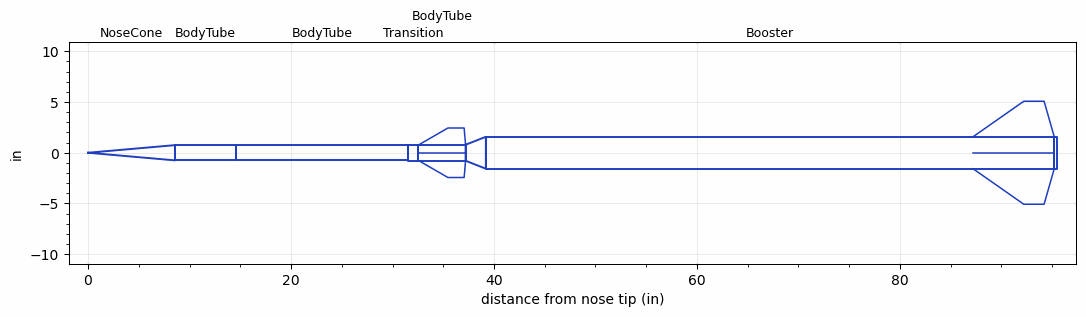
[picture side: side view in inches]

<RASAeroDocument>
 <FileVersion>2</FileVersion>
 <RocketDesign>
  <NoseCone>
   <Length>8.57</Length>
   <Diameter>1.5</Diameter>
   <Shape>Conical</Shape>
   <BluntRadius>0.065</BluntRadius>
   <Location>0</Location>
  </NoseCone>
  <BodyTube>
   <Length>6</Length>
   <Diameter>1.5</Diameter>
   <Location>8.57</Location>
  </BodyTube>
  <BodyTube>
   <Length>16.98</Length>
   <Diameter>1.5</Diameter>
   <Location>14.57</Location>
  </BodyTube>
  <Transition>
   <Length>1</Length>
   <Diameter>1.575</Diameter>
   <Location>31.55</Location>
   <RearDiameter>1.575</RearDiameter>
  </Transition>
  <BodyTube>
   <Length>4.65</Length>
   <Diameter>1.575</Diameter>
   <Location>32.55</Location>
   <Fin>
    <Count>4</Count>
    <Chord>4.6</Chord>
    <Span>1.65</Span>
    <SweepDistance>2.857</SweepDistance>
    <TipChord>1.6</TipChord>
    <Thickness>0.1</Thickness>
    <LERadius>0.024</LERadius>
    <Location>4.6</Location>
    <AirfoilSection>Double Wedge</AirfoilSection>
    <FX1>0.75</FX1>
    <FX3>0.25</FX3>
   </Fin>
  </BodyTube>
  <Booster>
   <Length>56</Length>
   <Diameter>3.15</Diameter>
   <InsideDiameter>1.575</InsideDiameter>
   <RailGuideDiameter>0.3</RailGuideDiameter>
   <RailGuideHeight>0.3</RailGuideHeight>
   <Location>37.2</Location>
   <ShoulderLength>2</ShoulderLength>
   <BoattailLength>0.25</BoattailLength>
   <BoattailRearDiameter>3.15</BoattailRearDiameter>
   <Fin>
    <Count>4</Count>
    <Chord>8</Chord>
    <Span>3.5</Span>
    <SweepDistance>5</SweepDistance>
    <TipChord>2</TipChord>
    <Thickness>0.1875</Thickness>
    <LERadius>0.065</LERadius>
    <Location>8</Location>
    <AirfoilSection>Hexagonal</AirfoilSection>
    <FX1>0.5</FX1>
    <FX3>0.5</FX3>
   </Fin>
  </Booster>
  <Surface>Camouflage Paint</Surface>
  <ModifiedBarrowman>True</ModifiedBarrowman>
  <Turbulence>True</Turbulence>
  <UseBooster1>False</UseBooster1>
  <UseBooster2>False</UseBooster2>
 </RocketDesign>
 <LaunchSite>
  <Altitude>2000</Altitude>
  <Pressure>29.9</Pressure>
  <RodAngle>5</RodAngle>
  <RodLength>15</RodLength>
  <Temperature>110</Temperature>
  <WindSpeed>10</WindSpeed>
 </LaunchSite>
 <Recovery>
  <Altitude1>1000</Altitude1>
  <Altitude2>1000</Altitude2>
  <DeviceType1>None</DeviceType1>
  <DeviceType2>None</DeviceType2>
  <Event1>False</Event1>
  <Event2>False</Event2>
  <Size1>1</Size1>
  <Size2>1</Size2>
  <EventType1>None</EventType1>
  <EventType2>None</EventType2>
  <CD1>1.33</CD1>
  <CD2>1.33</CD2>
 </Recovery>
 <SimulationList>
  <Simulation>
   <SustainerEngine>K478  (Polaris)</SustainerEngine>
   <SustainerLaunchWt>3.33</SustainerLaunchWt>
   <SustainerNozzleDiameter>1.325</SustainerNozzleDiameter>
   <SustainerCG>21.86</SustainerCG>
   <SustainerIgnitionDelay>8</SustainerIgnitionDelay>
   <Booster1Engine>N3114RR  (Walter)</Booster1Engine>
   <Booster1LaunchWt>24</Booster1LaunchWt>
   <Booster1SeparationDelay>0</Booster1SeparationDelay>
   <Booster1IgnitionDelay>0</Booster1IgnitionDelay>
   <Booster1CG>62</Booster1CG>
   <Booster1NozzleDiameter>3</Booster1NozzleDiameter>
   <IncludeBooster1>True</IncludeBooster1>
   <Booster2Delay>0</Booster2Delay>
   <IncludeBooster2>False</IncludeBooster2>
   <TimetoApogee>89.51996</TimetoApogee>
   <MaxAltitude>135442.8</MaxAltitude>
   <MaxVelocity>4906.483</MaxVelocity>
   <OptimumWt>4.1625</OptimumWt>
   <OptimumMaxAlt>4.1625</OptimumMaxAlt>
  </Simulation>
 </SimulationList>
</RASAeroDocument>
